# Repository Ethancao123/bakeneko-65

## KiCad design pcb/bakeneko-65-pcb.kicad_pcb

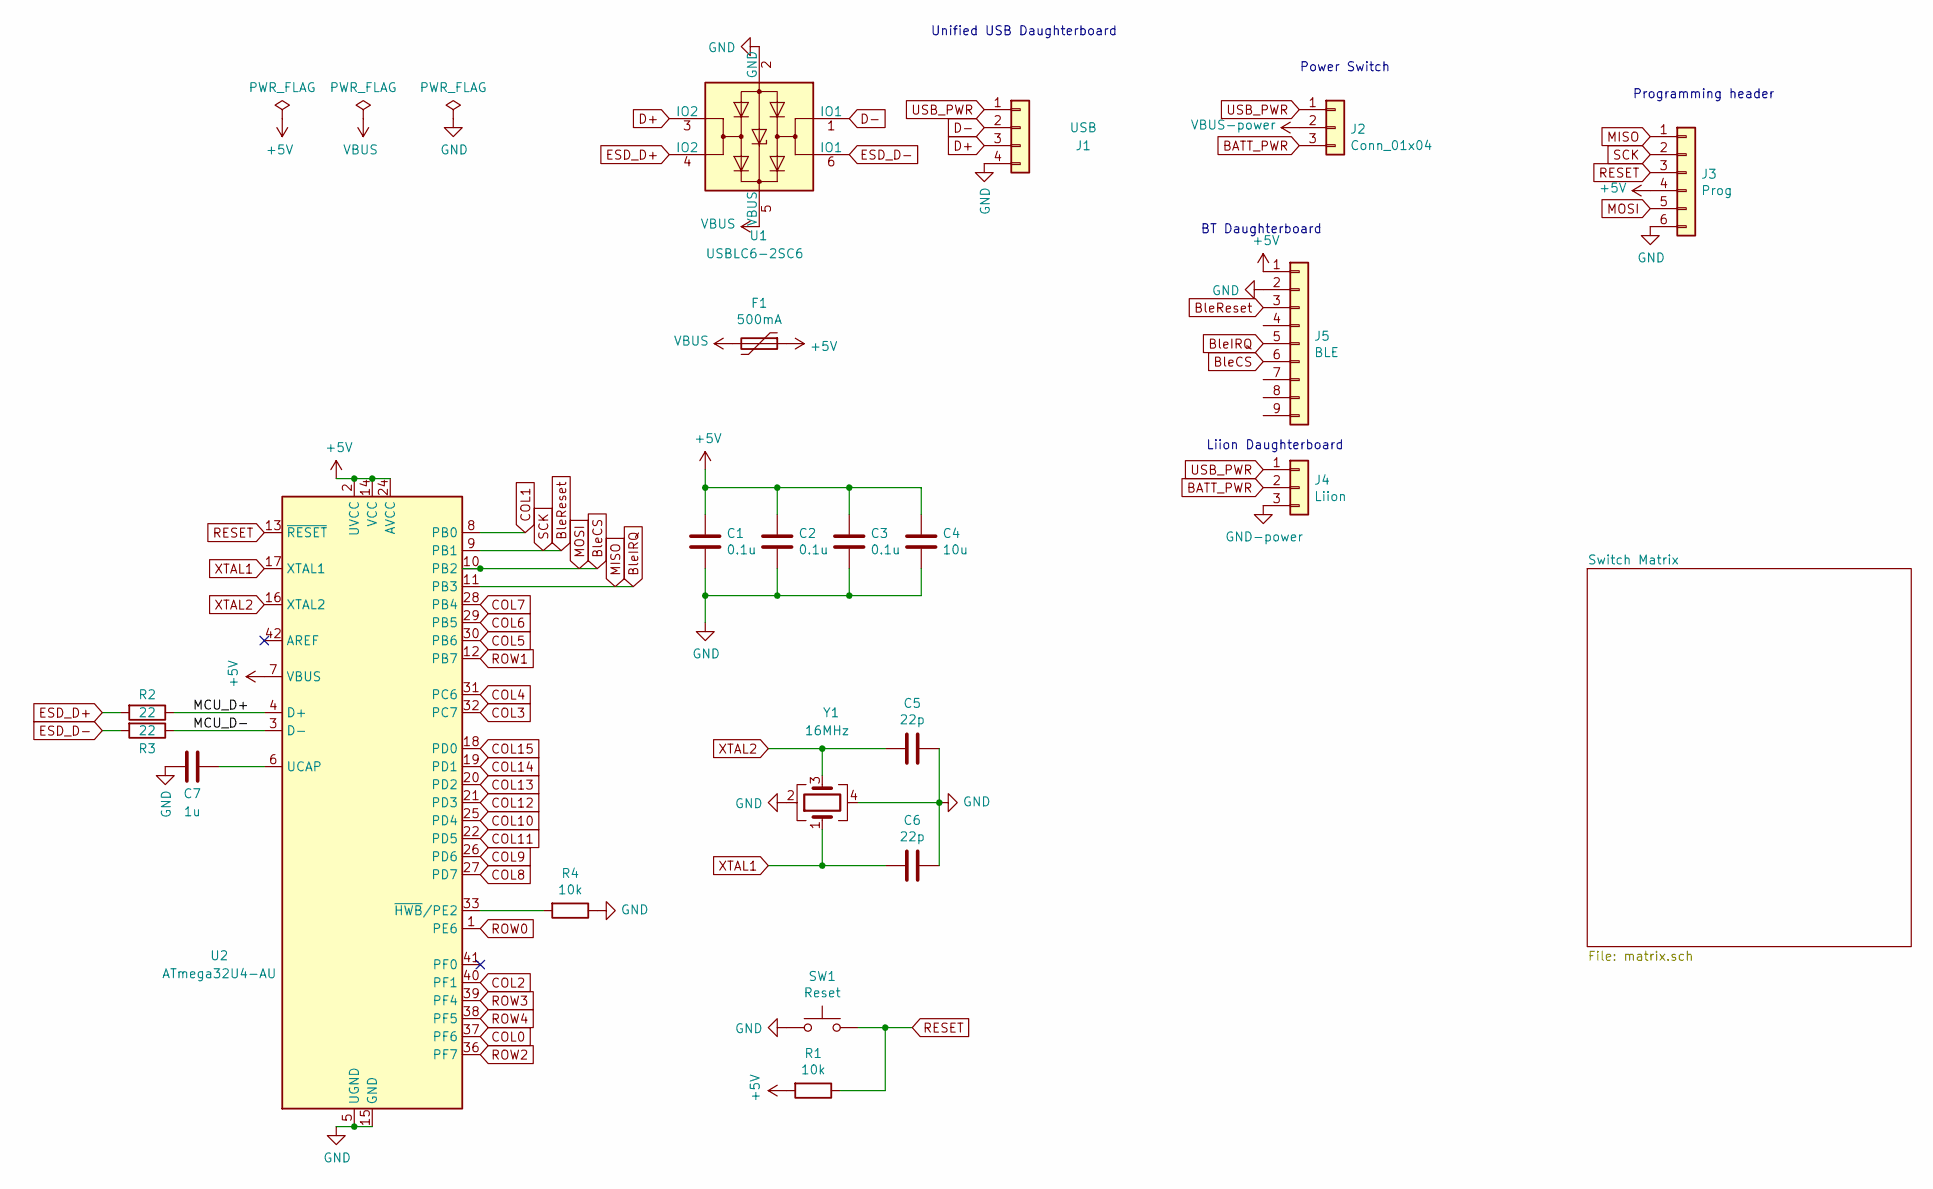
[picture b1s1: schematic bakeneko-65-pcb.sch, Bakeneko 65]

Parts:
C1, C2, C3: 0.1u; C_0805_2012Metric; LCSC Part # C49678
C4: 10u; C_0805_2012Metric; LCSC Part # C15850
C5, C6: 22p; C_0805_2012Metric; LCSC Part # C1804
C7: 1u; C_0805_2012Metric; LCSC Part # C28323
F1: 500mA; Fuse_1206_3216Metric; LCSC Part # C70076
J1: USB; JST_SH_SM04B-SRSS-TB_1x04-1MP_P1.00mm_Horizontal; LCSC Part # C160404
J2: Conn_01x04; JST_SH_BM03B-SRSS-TB_1x03-1MP_P1.00mm_Vertical
J3: Prog; PinHeader_1x06_P2.54mm_Vertical
J4: Liion; JST_SH_BM03B-SRSS-TB_1x03-1MP_P1.00mm_Vertical
J5: BLE; PinHeader_1x09_P2.54mm_Vertical
R1, R4: 10k; R_0805_2012Metric; LCSC Part # C17414
R2, R3: 22; R_0805_2012Metric; LCSC Part # C17561
SW1: Reset; SW_SPST_TL3342; LCSC Part # C318884
U1: USBLC6-2SC6; SOT-23-6; LCSC Part # C7519
U2: ATmega32U4-AU; TQFP-44_10x10mm_P0.8mm; LCSC Part # C44854
Y1: 16MHz; Crystal_SMD_3225-4Pin_3.2x2.5mm; LCSC Part # C13738

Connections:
+5V: C1.1, C2.1, C3.1, C4.1, F1.1, J3.4, J5.1, R1.2, U2.2 (UVCC), U2.7 (VBUS), U2.14 (VCC), U2.24 (AVCC), U2.34 (VCC), U2.44 (AVCC)
/MCU_D+: R2.1, U2.4 (D+)
/MCU_D-: R3.1, U2.3 (D-)
BATT_PWR: J2.3, J4.2
BleCS: J3.5, J5.6, U2.10 (PB2)
BleIRQ: J3.1, J5.5, U2.11 (PB3)
BleReset: J3.2, J5.3, U2.9 (PB1)
COL0: U2.37 (PF6); also elsewhere on the board
COL1: U2.8 (PB0); also elsewhere on the board
COL2: U2.40 (PF1); also elsewhere on the board
COL3: U2.32 (PC7); also elsewhere on the board
COL4: U2.31 (PC6); also elsewhere on the board
COL5: U2.30 (PB6); also elsewhere on the board
COL6: U2.29 (PB5); also elsewhere on the board
COL7: U2.28 (PB4); also elsewhere on the board
COL8: U2.27 (PD7); also elsewhere on the board
COL9: U2.26 (PD6); also elsewhere on the board
COL10: U2.25 (PD4); also elsewhere on the board
COL11: U2.22 (PD5); also elsewhere on the board
COL12: U2.21 (PD3); also elsewhere on the board
COL13: U2.20 (PD2); also elsewhere on the board
COL14: U2.19 (PD1); also elsewhere on the board
COL15: U2.18 (PD0); also elsewhere on the board
D+: J1.3, U1.3 (IO2)
D-: J1.2, U1.1 (IO1)
ESD_D+: R2.2, U1.4 (IO2)
ESD_D-: R3.2, U1.6 (IO1)
unnamed: C7.1, U2.6 (UCAP)
unnamed: R4.2, U2.33 (~HWB~/PE2)
RESET: J3.3, R1.1, SW1.2, U2.13 (~RESET)
ROW0: U2.1 (PE6); also elsewhere on the board
ROW1: U2.12 (PB7); also elsewhere on the board
ROW2: U2.36 (PF7); also elsewhere on the board
ROW3: U2.39 (PF4); also elsewhere on the board
ROW4: U2.38 (PF5); also elsewhere on the board
USB_PWR: J1.1, J2.1, J4.1
XTAL1: C6.2, U2.17 (XTAL1), Y1.1
XTAL2: C5.2, U2.16 (XTAL2), Y1.3

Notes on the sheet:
Programming header
Unified USB Daughterboard
Power Switch
BT Daughterboard
Liion Daughterboard

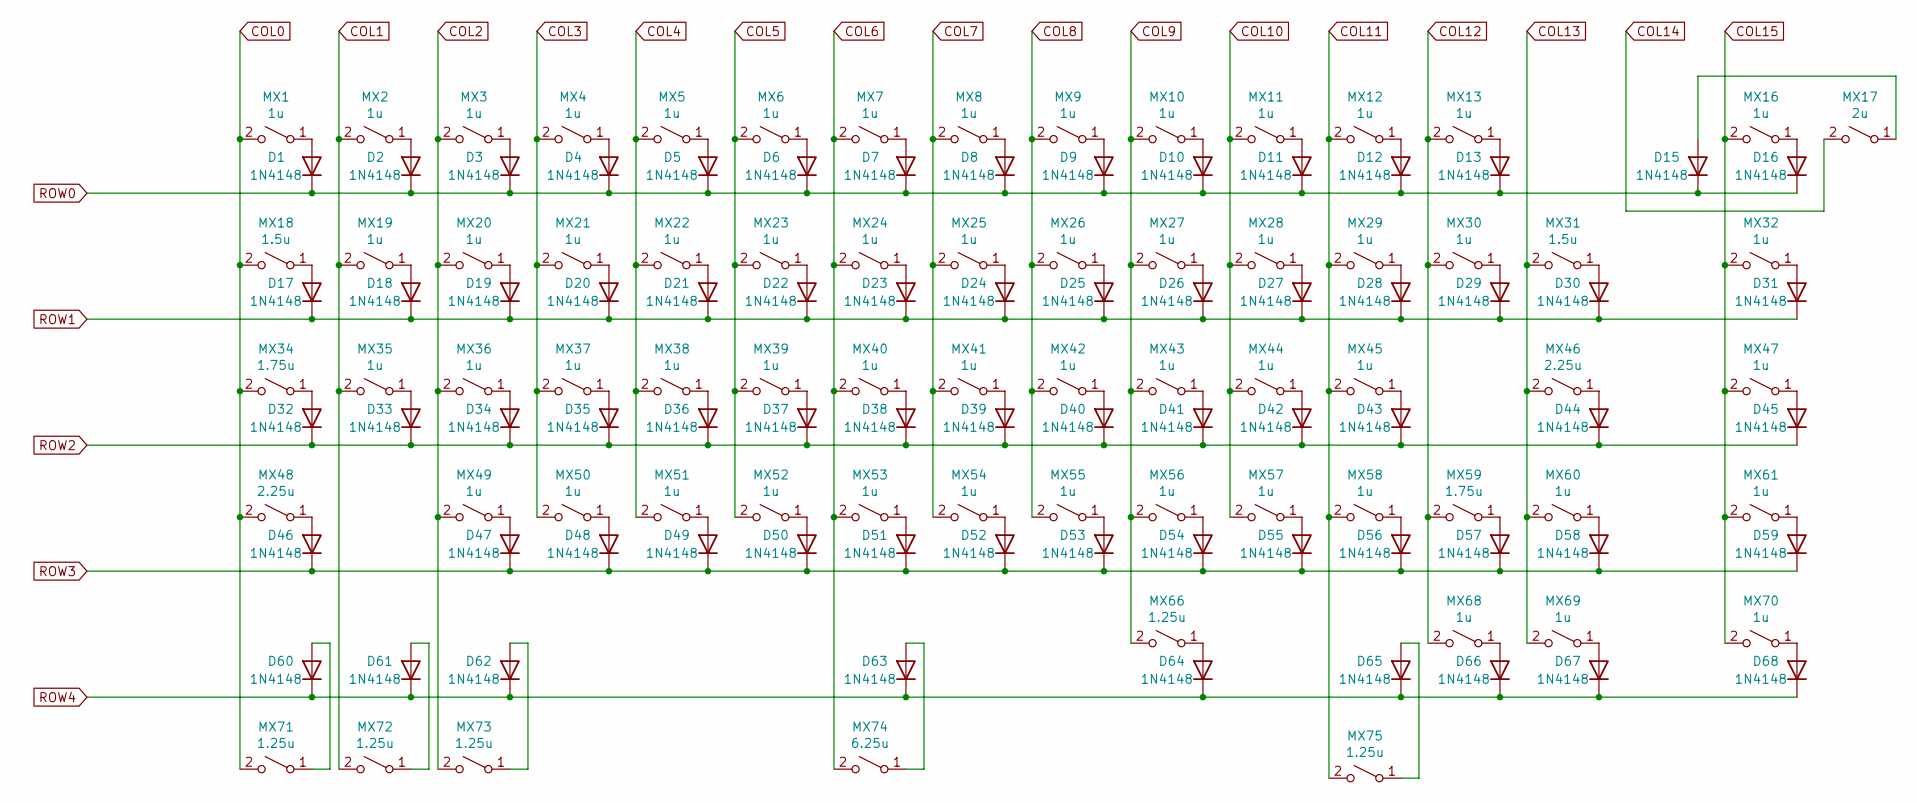
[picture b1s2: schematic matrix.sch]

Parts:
D1, D2, D3, D4, D5, D6, D7, D8, D9, D10, D11, D12, D13, D15, D16, D17, D18, D19, D20, D21, D22, D23, D24, D25, D26, D27, D28, D29, D30, D31, D32, D33, D34, D35, D36, D37, D38, D39, D40, D41, D42, D43, D44, D45, D46, D47, D48, D49, D50, D51, D52, D53, D54, D55, D56, D57, D58, D59, D60, D61, D62, D63, D64, D65, D66, D67, D68: 1N4148; D_SOD-123; LCSC Part # C81598
MX1, MX2, MX3, MX4, MX5, MX6, MX7, MX8, MX9, MX10, MX11, MX12, MX13, MX16, MX19, MX20, MX21, MX22, MX23, MX24, MX25, MX26, MX27, MX28, MX29, MX30, MX32, MX35, MX36, MX37, MX38, MX39, MX40, MX41, MX42, MX43, MX44, MX45, MX47, MX49, MX50, MX51, MX52, MX53, MX54, MX55, MX56, MX57, MX58, MX60, MX61, MX68, MX69, MX70: 1u; Kailh_socket_MX
MX17: 2u; MXOnly-2U-Hotswap
MX18, MX31: 1.5u; MXOnly-1.5U-Hotswap
MX34, MX59: 1.75u; MXOnly-1.75U-Hotswap
MX46, MX48: 2.25u; MXOnly-2.25U-Hotswap
MX66, MX71, MX72, MX73, MX75: 1.25u; MXOnly-1.25U-Hotswap
MX74: 6.25u; MXOnly-6.25U-Hotswap-ReversedStabilizers

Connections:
COL0: MX1.2 (B), MX18.2 (B), MX34.2 (B), MX48.2 (B), MX71.2 (B); also elsewhere on the board
COL1: MX2.2 (B), MX19.2 (B), MX35.2 (B), MX72.2 (B); also elsewhere on the board
COL2: MX3.2 (B), MX20.2 (B), MX36.2 (B), MX49.2 (B), MX73.2 (B); also elsewhere on the board
COL3: MX4.2 (B), MX21.2 (B), MX37.2 (B), MX50.2 (B); also elsewhere on the board
COL4: MX5.2 (B), MX22.2 (B), MX38.2 (B), MX51.2 (B); also elsewhere on the board
COL5: MX6.2 (B), MX23.2 (B), MX39.2 (B), MX52.2 (B); also elsewhere on the board
COL6: MX7.2 (B), MX24.2 (B), MX40.2 (B), MX53.2 (B), MX74.2 (B); also elsewhere on the board
COL7: MX8.2 (B), MX25.2 (B), MX41.2 (B), MX54.2 (B); also elsewhere on the board
COL8: MX9.2 (B), MX26.2 (B), MX42.2 (B), MX55.2 (B); also elsewhere on the board
COL9: MX10.2 (B), MX27.2 (B), MX43.2 (B), MX56.2 (B), MX66.2 (B); also elsewhere on the board
COL10: MX11.2 (B), MX28.2 (B), MX44.2 (B), MX57.2 (B); also elsewhere on the board
COL11: MX12.2 (B), MX29.2 (B), MX45.2 (B), MX58.2 (B), MX75.2 (B); also elsewhere on the board
COL12: MX13.2 (B), MX30.2 (B), MX59.2 (B), MX68.2 (B); also elsewhere on the board
COL13: MX31.2 (B), MX46.2 (B), MX60.2 (B), MX69.2 (B); also elsewhere on the board
COL14: MX17.2 (B); also elsewhere on the board
COL15: MX16.2 (B), MX32.2 (B), MX47.2 (B), MX61.2 (B), MX70.2 (B); also elsewhere on the board
unnamed: D1.2 (A), MX1.1 (A)
unnamed: D2.2 (A), MX2.1 (A)
unnamed: D3.2 (A), MX3.1 (A)
unnamed: D4.2 (A), MX4.1 (A)
unnamed: D5.2 (A), MX5.1 (A)
unnamed: D6.2 (A), MX6.1 (A)
unnamed: D7.2 (A), MX7.1 (A)
unnamed: D8.2 (A), MX8.1 (A)
unnamed: D9.2 (A), MX9.1 (A)
unnamed: D10.2 (A), MX10.1 (A)
unnamed: D11.2 (A), MX11.1 (A)
unnamed: D12.2 (A), MX12.1 (A)
unnamed: D13.2 (A), MX13.1 (A)
unnamed: D15.2 (A), MX17.1 (A)
unnamed: D16.2 (A), MX16.1 (A)
unnamed: D17.2 (A), MX18.1 (A)
unnamed: D18.2 (A), MX19.1 (A)
unnamed: D19.2 (A), MX20.1 (A)
unnamed: D20.2 (A), MX21.1 (A)
unnamed: D21.2 (A), MX22.1 (A)
unnamed: D22.2 (A), MX23.1 (A)
unnamed: D23.2 (A), MX24.1 (A)
unnamed: D24.2 (A), MX25.1 (A)
unnamed: D25.2 (A), MX26.1 (A)
unnamed: D26.2 (A), MX27.1 (A)
unnamed: D27.2 (A), MX28.1 (A)
unnamed: D28.2 (A), MX29.1 (A)
unnamed: D29.2 (A), MX30.1 (A)
unnamed: D30.2 (A), MX31.1 (A)
unnamed: D31.2 (A), MX32.1 (A)
unnamed: D32.2 (A), MX34.1 (A)
unnamed: D33.2 (A), MX35.1 (A)
unnamed: D34.2 (A), MX36.1 (A)
unnamed: D35.2 (A), MX37.1 (A)
unnamed: D36.2 (A), MX38.1 (A)
unnamed: D37.2 (A), MX39.1 (A)
unnamed: D38.2 (A), MX40.1 (A)
unnamed: D39.2 (A), MX41.1 (A)
unnamed: D40.2 (A), MX42.1 (A)
unnamed: D41.2 (A), MX43.1 (A)
unnamed: D42.2 (A), MX44.1 (A)
unnamed: D43.2 (A), MX45.1 (A)
unnamed: D44.2 (A), MX46.1 (A)
unnamed: D45.2 (A), MX47.1 (A)
unnamed: D46.2 (A), MX48.1 (A)
unnamed: D47.2 (A), MX49.1 (A)
unnamed: D48.2 (A), MX50.1 (A)
unnamed: D49.2 (A), MX51.1 (A)
unnamed: D50.2 (A), MX52.1 (A)
unnamed: D51.2 (A), MX53.1 (A)
unnamed: D52.2 (A), MX54.1 (A)
unnamed: D53.2 (A), MX55.1 (A)
unnamed: D54.2 (A), MX56.1 (A)
unnamed: D55.2 (A), MX57.1 (A)
unnamed: D56.2 (A), MX58.1 (A)
unnamed: D57.2 (A), MX59.1 (A)
unnamed: D58.2 (A), MX60.1 (A)
unnamed: D59.2 (A), MX61.1 (A)
unnamed: D60.2 (A), MX71.1 (A)
unnamed: D61.2 (A), MX72.1 (A)
unnamed: D62.2 (A), MX73.1 (A)
unnamed: D63.2 (A), MX74.1 (A)
unnamed: D64.2 (A), MX66.1 (A)
unnamed: D65.2 (A), MX75.1 (A)
unnamed: D66.2 (A), MX68.1 (A)
unnamed: D67.2 (A), MX69.1 (A)
unnamed: D68.2 (A), MX70.1 (A)
ROW0: D1.1 (K), D2.1 (K), D3.1 (K), D4.1 (K), D5.1 (K), D6.1 (K), D7.1 (K), D8.1 (K), D9.1 (K), D10.1 (K), D11.1 (K), D12.1 (K), D13.1 (K), D15.1 (K), D16.1 (K); also elsewhere on the board
ROW1: D17.1 (K), D18.1 (K), D19.1 (K), D20.1 (K), D21.1 (K), D22.1 (K), D23.1 (K), D24.1 (K), D25.1 (K), D26.1 (K), D27.1 (K), D28.1 (K), D29.1 (K), D30.1 (K), D31.1 (K); also elsewhere on the board
ROW2: D32.1 (K), D33.1 (K), D34.1 (K), D35.1 (K), D36.1 (K), D37.1 (K), D38.1 (K), D39.1 (K), D40.1 (K), D41.1 (K), D42.1 (K), D43.1 (K), D44.1 (K), D45.1 (K); also elsewhere on the board
ROW3: D46.1 (K), D47.1 (K), D48.1 (K), D49.1 (K), D50.1 (K), D51.1 (K), D52.1 (K), D53.1 (K), D54.1 (K), D55.1 (K), D56.1 (K), D57.1 (K), D58.1 (K), D59.1 (K); also elsewhere on the board
ROW4: D60.1 (K), D61.1 (K), D62.1 (K), D63.1 (K), D64.1 (K), D65.1 (K), D66.1 (K), D67.1 (K), D68.1 (K); also elsewhere on the board

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
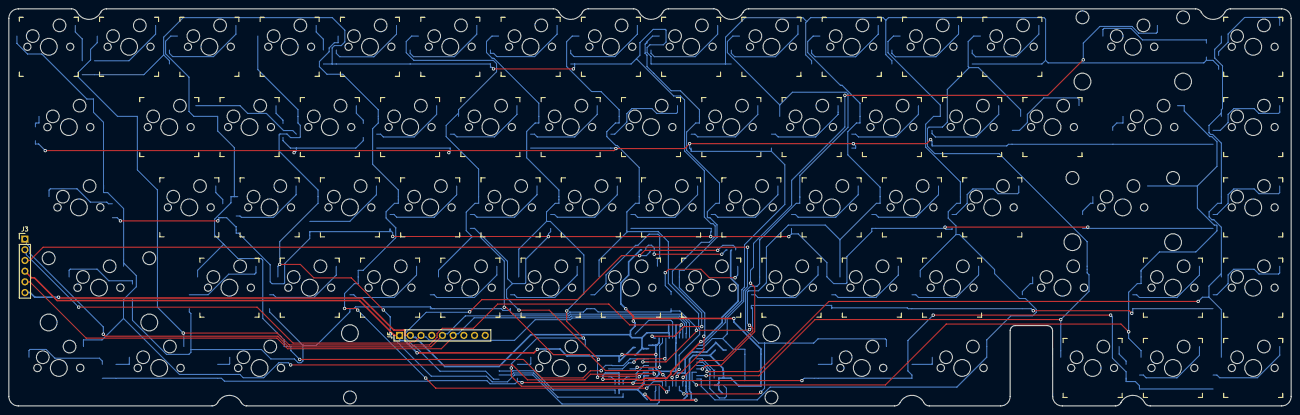
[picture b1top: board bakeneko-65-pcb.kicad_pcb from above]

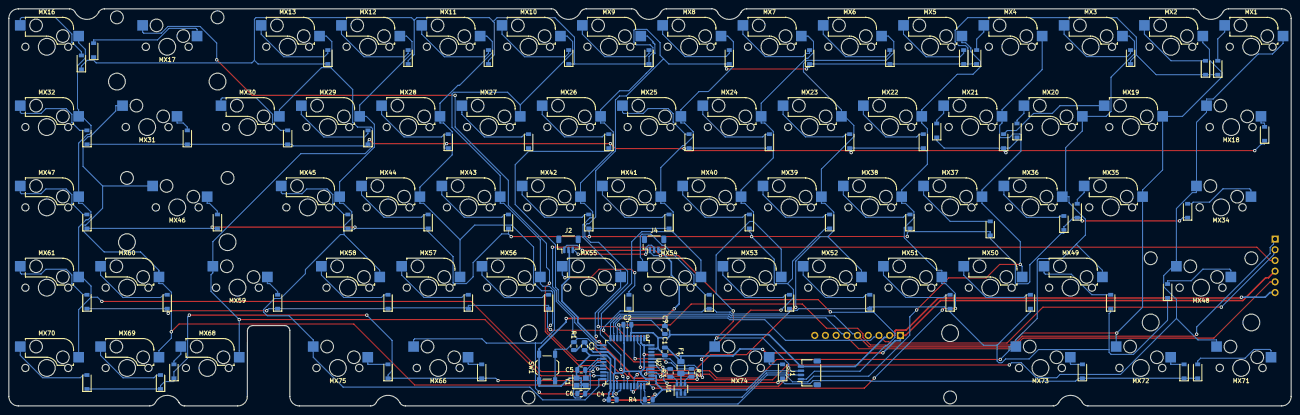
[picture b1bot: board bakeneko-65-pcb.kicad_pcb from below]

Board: 2 copper layers, 304.2 x 94.2 mm, 155 parts (86 on the bottom side), 107 nets.

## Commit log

2021-05-23 [ImgBot] Optimize images
    *Total -- 391.45kb -> 273.45kb (30.14%)
    /image/keyboard-layout.png -- 34.99kb -> 19.32kb (44.78%)
    /image/bakeneko-65-draft.png -- 162.62kb -> 97.77kb (39.88%)
    /image/bakeneko-65-pcb-bottom.png -- 113.59kb -> 89.97kb (20.79%)
    /image/bakeneko-65-pcb-top.png -- 80.25kb -> 66.39kb (17.27%)
2021-05-31 Added hotswap
2021-06-16 finished keyboard pcb
